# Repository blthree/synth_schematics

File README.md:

View this project on [CADLAB.io](https://cadlab.io/project/1908). 

# synth_schematics

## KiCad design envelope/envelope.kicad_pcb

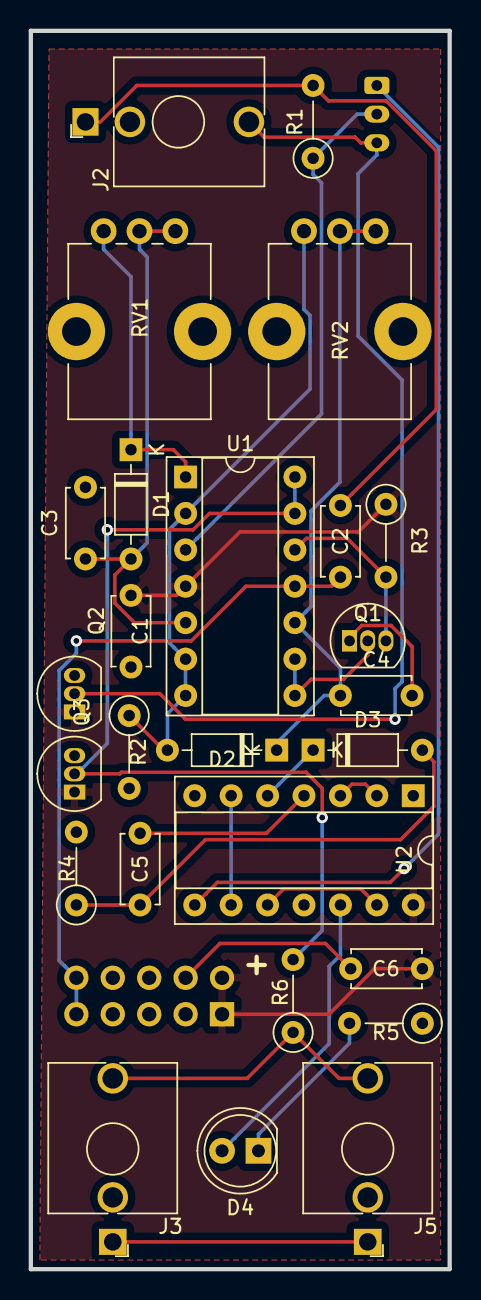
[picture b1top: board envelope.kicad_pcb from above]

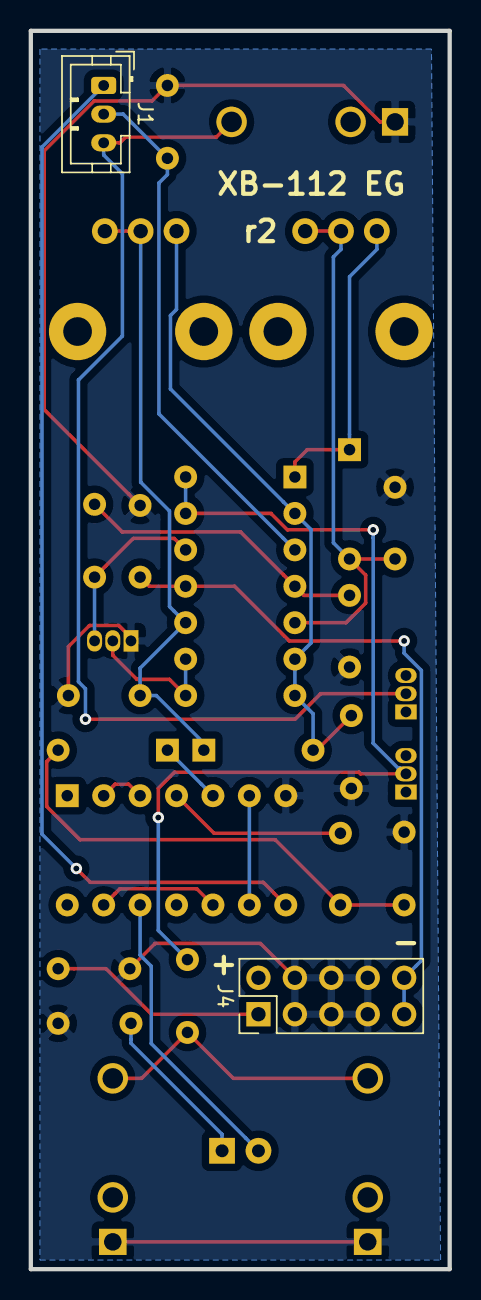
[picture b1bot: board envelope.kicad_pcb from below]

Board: 2 copper layers, 29.2 x 86.4 mm, 28 parts (2 on the bottom side), 22 nets.

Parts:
C1, C2, C6: 0.1uF; C_Disc_D4.7mm_W2.5mm_P5.00mm
C3, C4, C5: 1uF; C_Disc_D4.7mm_W2.5mm_P5.00mm
D1, D2: D_ALT; D_DO-35_SOD27_P7.62mm_Horizontal
D3: 1N4148; D_DO-35_SOD27_P7.62mm_Horizontal
D4: LED; LED_D5.0mm
J1: Sustain; JST_PH_B3B-PH-K_1x03_P2.00mm_Vertical
J2: Gate In; Jack_3.5mm_QingPu_WQP-PJ398SM_Vertical_CircularHoles
J3: Env Out 1; Jack_3.5mm_QingPu_WQP-PJ398SM_Vertical_CircularHoles
J4: Power; PinHeader_2x05_P2.54mm_Vertical
J5: Env Out 2; Jack_3.5mm_QingPu_WQP-PJ398SM_Vertical_CircularHoles
Q1: 2N3906; TO-92_Inline
Q2, Q3: BC548; TO-92_Inline
R1, R2: 1M; R_Axial_DIN0207_L6.3mm_D2.5mm_P5.08mm_Vertical
R3, R4: 100K; R_Axial_DIN0207_L6.3mm_D2.5mm_P5.08mm_Vertical
R5, R6: 1K; R_Axial_DIN0207_L6.3mm_D2.5mm_P5.08mm_Vertical
RV1: 1M Attack; Potentiometer_Bourns_PTV09A-1_Single_Vertical
RV2: 1M Decay; Potentiometer_Bourns_PTV09A-1_Single_Vertical
U1: TL074; DIP-14_W7.62mm_Socket
U2: 40106; DIP-14_W7.62mm_Socket

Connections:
+9V: C1.1, C6.1, J4.1, J4.2, Q2.1, Q3.1, R3.1, U1.4, U2.14
-9V: C2.1, J4.9, J4.10, U1.11
EG: J3.T, J5.T, R6.1
EG_In: J1.2, R1.1, U1.3
GND: C1.2, C2.2, C3.2, C4.2, C6.2, J2.S, J3.S, J4.3, J4.4, J4.5, J4.6, J4.7, J4.8, J5.S, Q1.1, R1.2, R2.2, R4.2, R5.1, U2.7
Gate: J1.3, J2.T, Q2.2
unnamed: C3.1, D1.2, RV1.2, RV1.3, U1.5
unnamed: C4.1, D2.1, RV2.2, RV2.3, U1.10
unnamed: C5.1, D3.2, R4.1
unnamed: C5.2, U2.4
unnamed: D1.1, RV1.1, U1.1
unnamed: D2.2, R2.1, RV2.1, U1.2, U1.6, U1.7
unnamed: D3.1, U2.5
unnamed: D4.1, R5.2
unnamed: D4.2, U2.12
unnamed: Q1.2, U1.8, U1.9
unnamed: Q1.3, R3.2, U1.12
unnamed: Q3.2, R6.2, U1.13, U1.14
unnamed: U2.2, U2.3
unnamed: U2.6, U2.9
unnamed: U2.10, U2.13
Trigger: J1.1, U2.8

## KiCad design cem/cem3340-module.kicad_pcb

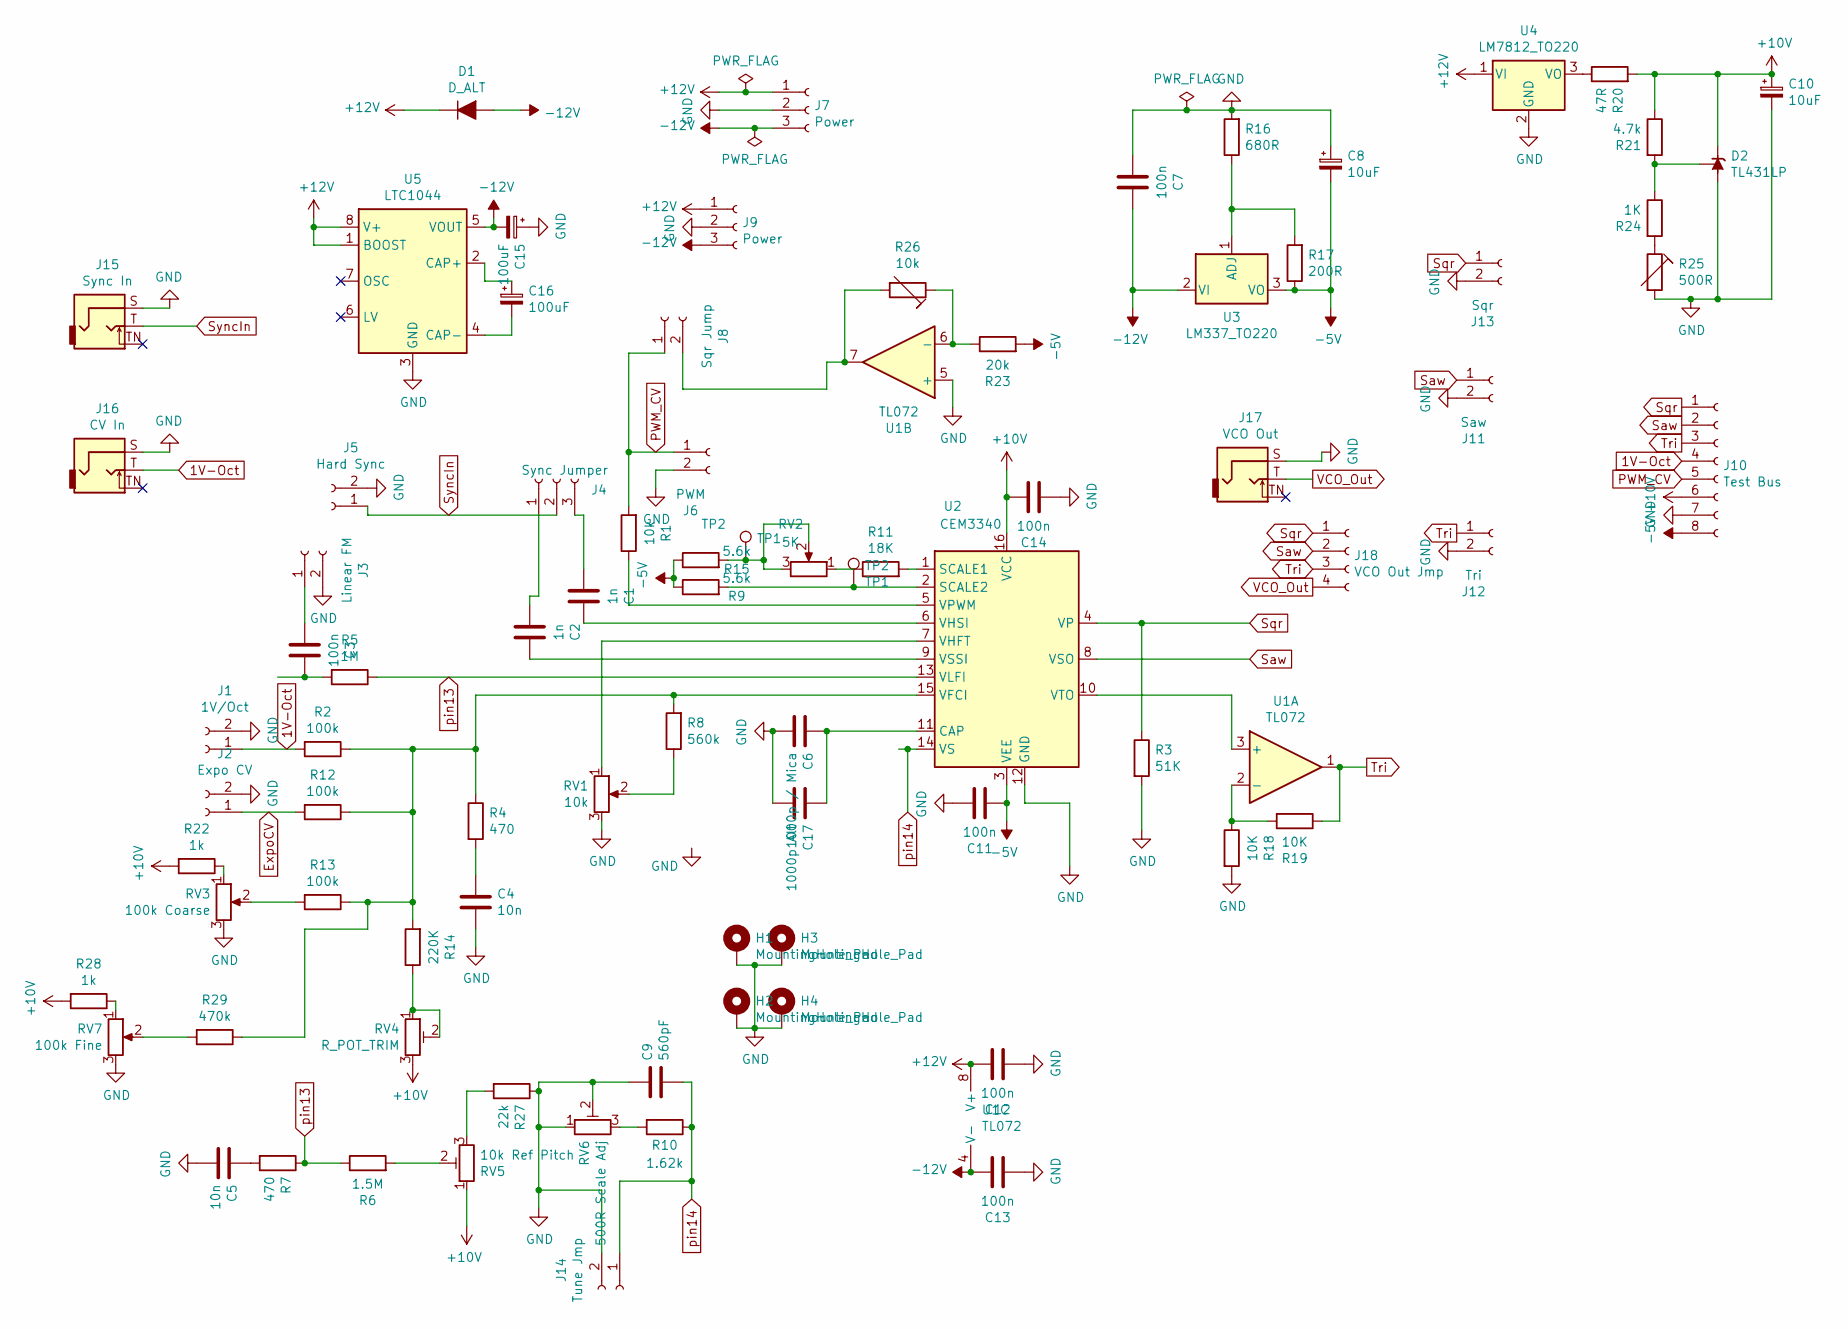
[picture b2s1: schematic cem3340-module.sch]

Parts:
C1, C2: 1n; C_Disc_D4.7mm_W2.5mm_P5.00mm
C3, C7, C11, C12, C13, C14: 100n; C_Disc_D4.7mm_W2.5mm_P5.00mm
C4, C5: 10n; C_Disc_D4.7mm_W2.5mm_P5.00mm
C6: 1000p / Mica; C_Axial_L12.0mm_D6.5mm_P15.00mm_Horizontal
C8, C10: 10uF; CP_Radial_D7.5mm_P2.50mm
C9: 560pF; C_Disc_D4.7mm_W2.5mm_P5.00mm
C15, C16: 100uF; CP_Radial_D7.5mm_P2.50mm
C17: 1000p Alt; C_Rect_L10.0mm_W4.0mm_P7.50mm_MKS4
D1: D_ALT; D_DO-35_SOD27_P7.62mm_Horizontal
D2: TL431LP; TO-92_Inline
H1, H2, H3, H4: MountingHole_Pad; MountingHole_3.2mm_M3_ISO14580_Pad
J1: 1V/Oct; PinHeader_1x02_P2.54mm_Vertical
J2: Expo CV; PinHeader_1x02_P2.54mm_Vertical
J3: Linear FM; PinHeader_1x02_P2.54mm_Vertical
J4: Sync Jumper; PinHeader_1x03_P2.54mm_Vertical
J5: Hard Sync; PinHeader_1x02_P2.54mm_Vertical
J6: PWM; PinHeader_1x02_P2.54mm_Vertical
J7: Power; JST_PH_B3B-PH-K_1x03_P2.00mm_Vertical
J8: Sqr Jump; PinHeader_1x02_P2.54mm_Vertical
J9: Power; JST_XH_B03B-XH-AM_1x03_P2.50mm_Vertical
J10: Test Bus; PinHeader_1x08_P2.54mm_Vertical
J11: Saw; PinHeader_1x02_P2.54mm_Vertical
J12: Tri; PinHeader_1x02_P2.54mm_Vertical
J13: Sqr; PinHeader_1x02_P2.54mm_Vertical
J14: Tune Jmp; PinHeader_1x02_P2.54mm_Vertical
J15: Sync In; CUI_SJ2-3592B-SMT-TR
J16: CV In; CUI_SJ2-3592B-SMT-TR
J17: VCO Out; CUI_SJ2-3592B-SMT-TR
J18: VCO Out Jmp; PinHeader_1x04_P2.54mm_Vertical
R1: 10k; R_Axial_DIN0207_L6.3mm_D2.5mm_P5.08mm_Vertical
R2, R12, R13: 100k; R_Axial_DIN0207_L6.3mm_D2.5mm_P5.08mm_Vertical
R3: 51K; R_Axial_DIN0207_L6.3mm_D2.5mm_P5.08mm_Vertical
R4, R7: 470; R_Axial_DIN0207_L6.3mm_D2.5mm_P5.08mm_Vertical
R5: 1M; R_Axial_DIN0207_L6.3mm_D2.5mm_P5.08mm_Vertical
R6: 1.5M; R_Axial_DIN0207_L6.3mm_D2.5mm_P5.08mm_Vertical
R8: 560k; R_Axial_DIN0207_L6.3mm_D2.5mm_P5.08mm_Vertical
R9, R15: 5.6k; R_Axial_DIN0207_L6.3mm_D2.5mm_P5.08mm_Vertical
R10: 1.62k; R_Axial_DIN0207_L6.3mm_D2.5mm_P5.08mm_Vertical
R11: 18K; R_Axial_DIN0207_L6.3mm_D2.5mm_P5.08mm_Vertical
R14: 220K; R_Axial_DIN0207_L6.3mm_D2.5mm_P5.08mm_Vertical
R16: 680R; R_Axial_DIN0207_L6.3mm_D2.5mm_P5.08mm_Vertical
R17: 200R; R_Axial_DIN0207_L6.3mm_D2.5mm_P5.08mm_Vertical
R18, R19: 10K; R_Axial_DIN0207_L6.3mm_D2.5mm_P5.08mm_Vertical
R20: 47R; R_Axial_DIN0207_L6.3mm_D2.5mm_P5.08mm_Vertical
R21: 4.7k; R_Axial_DIN0207_L6.3mm_D2.5mm_P5.08mm_Vertical
R22, R28: 1k; R_Axial_DIN0207_L6.3mm_D2.5mm_P5.08mm_Vertical
R23: 20k; R_Axial_DIN0207_L6.3mm_D2.5mm_P5.08mm_Vertical
R24: 1K; R_Axial_DIN0207_L6.3mm_D2.5mm_P5.08mm_Vertical
R25: 500R; Potentiometer_Bourns_3296W_Vertical
R26: 10k; Potentiometer_Bourns_3296W_Vertical
R27: 22k; R_Axial_DIN0207_L6.3mm_D2.5mm_P5.08mm_Vertical
R29: 470k; R_Axial_DIN0207_L6.3mm_D2.5mm_P5.08mm_Vertical
RV1: 10k; Potentiometer_Bourns_3296W_Vertical
RV2: 5K; Potentiometer_Bourns_3386P_Vertical
RV3: 100k Coarse; Potentiometer_Bourns_PTV09A-1_Single_Vertical
RV4: R_POT_TRIM; Potentiometer_Bourns_3296W_Vertical
RV5: 10k Ref Pitch; Potentiometer_Bourns_3296W_Vertical
RV6: 500R Scale Adj; Potentiometer_Bourns_3296W_Vertical
RV7: 100k Fine; Potentiometer_Bourns_PTV09A-1_Single_Vertical
TP1: TP2; TestPoint_Pad_2.5x2.5mm
TP2: TP1; TestPoint_Pad_D2.5mm
U1: TL072; DIP-8_W7.62mm_Socket
U2: CEM3340; DIP-16_W7.62mm_Socket
U3: LM337_TO220; TO-220-3_Horizontal_TabDown
U4: LM7812_TO220; TO-220-3_Horizontal_TabDown
U5: LTC1044; DIP-8_W7.62mm_Socket

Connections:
1V-Oct: J1.1, J10.4, J16.T, R2.2
+10V: C10.1, C14.1, D2.3 (K), J10.6, R20.2, R21.1, R22.2, R28.2, RV4.3, RV5.1, U2.16 (VCC)
+12V: C12.1, D1.1 (K), J7.1, J9.1, U1.8 (V+), U4.1 (VI), U5.1 (BOOST), U5.8 (V+)
-5V: C8.2, C11.2, J10.8, R9.1, R15.1, R17.1, R23.2, U2.3 (VEE), U3.3 (VO)
-12V: C7.1, C13.1, C15.2, D1.2 (A), J7.3, J9.3, U1.4 (V-), U3.2 (VI), U5.5 (VOUT)
ExpoCV: J2.1, R12.2
GND: C4.2, C5.2, C6.2, C7.2, C8.1, C9.1, C10.2, C11.1, C12.2, C13.2, C14.2, C15.1, C17.2, D2.2 (A), H1.1, H2.1, H3.1, H4.1, J1.2, J2.2, J3.2, J5.2, J6.2, J7.2, J9.2, J10.7, J11.2, J12.2, J13.2, J14.2, J15.S, J16.S, J17.S, R3.2, R16.2, R18.2, R25.2, R27.1, RV1.3, RV3.3, RV6.1, RV6.2, RV7.3, U1.5 (+), U2.12 (GND), U4.2 (GND), U5.3 (GND)
unnamed: C1.1, U2.6 (VHSI)
unnamed: C1.2, J4.3
unnamed: C2.1, U2.9 (VSSI)
unnamed: C2.2, J4.1
unnamed: C3.1, R5.2
unnamed: C3.2, J3.1
unnamed: C4.1, R4.2
unnamed: C5.1, R7.2
unnamed: C16.1, U5.2 (CAP+)
unnamed: C16.2, U5.4 (CAP-)
unnamed: C6.1, C17.1, U2.11 (CAP)
unnamed: D2.1 (REF), R21.2, R24.1
unnamed: J8.2, R26.2, U1.7
unnamed: R1.1, U2.5 (VPWM)
unnamed: R6.2, RV5.2
unnamed: R8.1, RV1.2
unnamed: R9.2, TP2.1, U2.2 (SCALE2)
unnamed: R10.2, RV6.3
unnamed: R11.1, RV2.1
unnamed: R11.2, U2.1 (SCALE1)
unnamed: R2.1, R4.1, R8.2, R12.1, R13.1, R14.2, R29.1, U2.15 (VFCI)
unnamed: R13.2, RV3.2
unnamed: R14.1, RV4.1, RV4.2
unnamed: R15.2, RV2.2, RV2.3, TP1.1
unnamed: R16.1, R17.2, U3.1 (ADJ)
unnamed: R18.1, R19.2, U1.2 (-)
unnamed: R20.1, U4.3 (VO)
unnamed: R22.1, RV3.1
unnamed: R23.1, R26.1, U1.6 (-)
unnamed: R24.2, R25.1
unnamed: R27.2, RV5.3
unnamed: R28.1, RV7.1
unnamed: R29.2, RV7.2
unnamed: RV1.1, U2.7 (VHFT)
unnamed: U1.3 (+), U2.10 (VTO)
PWM_CV: J6.1, J8.1, J10.5, R1.2
Saw: J10.2, J11.1, J18.2, U2.8 (VSO)
Sqr: J10.1, J13.1, J18.1, R3.1, U2.4 (VP)
SyncIn: J4.2, J5.1, J15.T
Tri: J10.3, J12.1, J18.3, R19.1, U1.1
VCO_Out: J17.T, J18.4
pin13: R5.1, R6.1, R7.1, U2.13 (VLFI)
pin14: C9.2, J14.1, R10.1, U2.14 (VS)

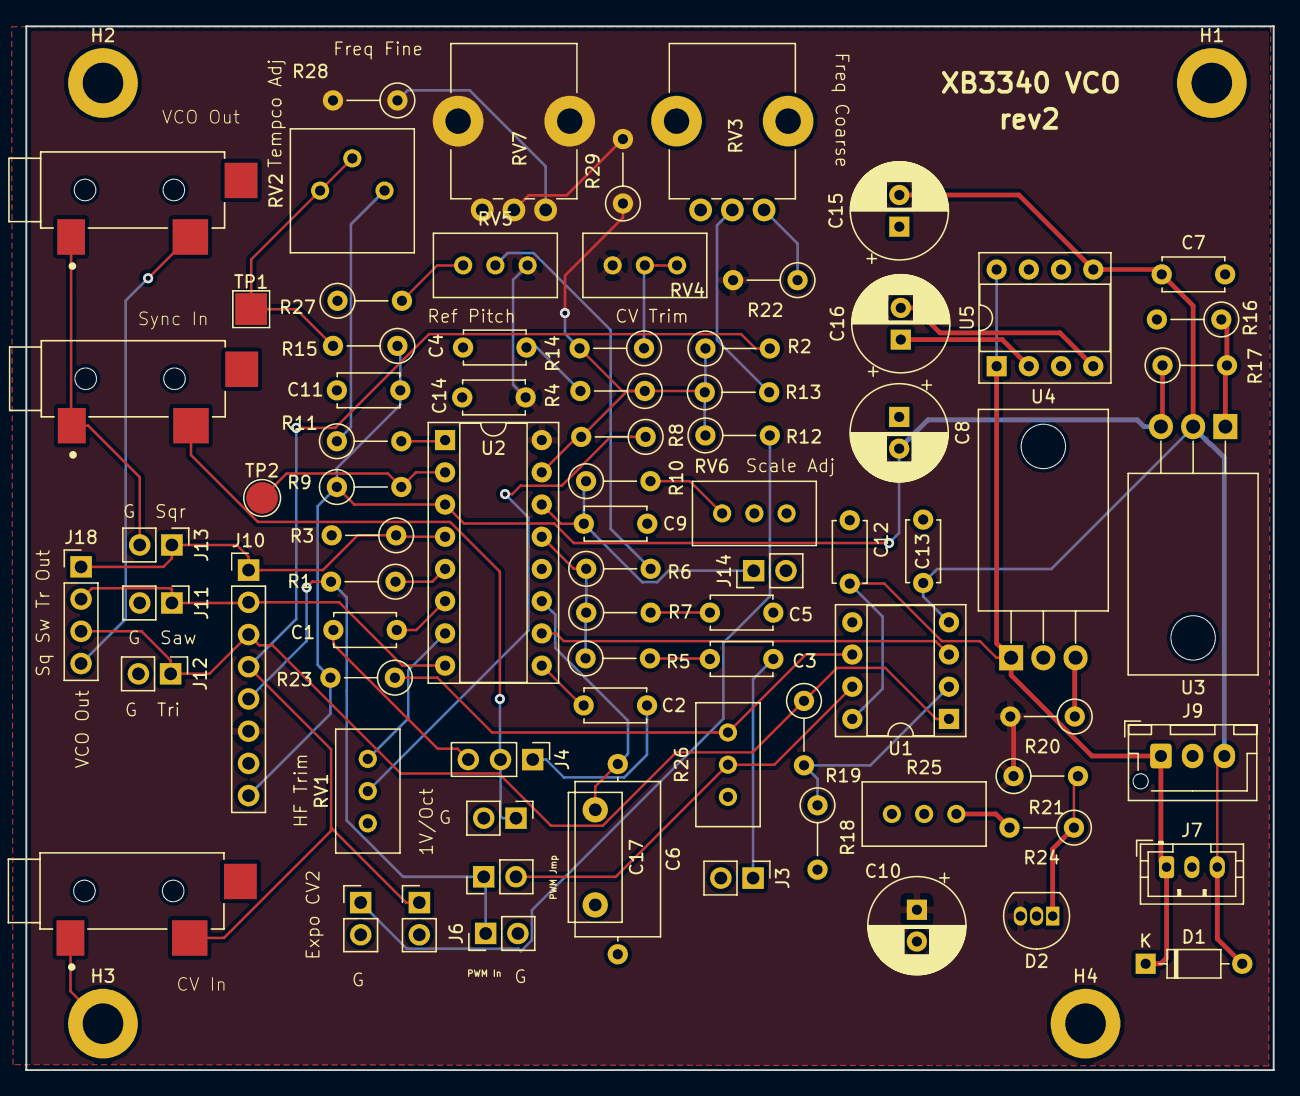
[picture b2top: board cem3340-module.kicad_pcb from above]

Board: 2 copper layers, 98.3 x 82.3 mm, 84 parts (0 on the bottom side), 50 nets.

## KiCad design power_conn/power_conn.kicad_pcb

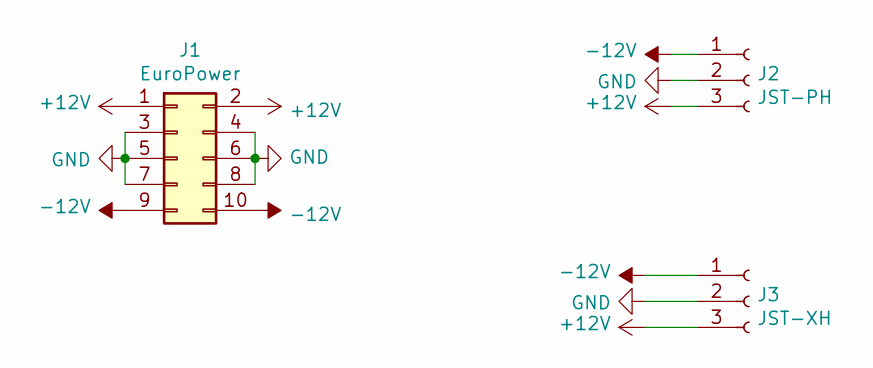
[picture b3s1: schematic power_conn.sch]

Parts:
J1: EuroPower; PinSocket_2x05_P2.54mm_Vertical
J2: JST-PH; JST_PH_B3B-PH-K_1x03_P2.00mm_Vertical
J3: JST-XH; JST_XH_B3B-XH-AM_1x03_P2.50mm_Vertical

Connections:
+12V: J1.1, J1.2, J2.3, J3.3
-12V: J1.9, J1.10, J2.1, J3.1
GND: J1.3, J1.4, J1.5, J1.6, J1.7, J1.8, J2.2, J3.2

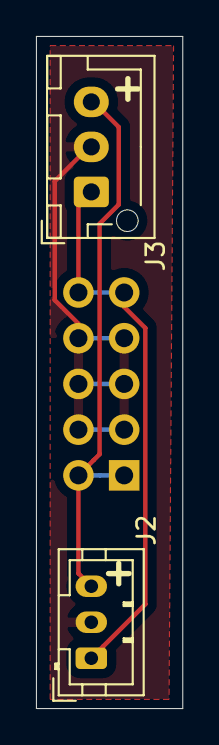
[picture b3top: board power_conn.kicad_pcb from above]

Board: 2 copper layers, 8.1 x 37.3 mm, 3 parts (1 on the bottom side), 3 nets.

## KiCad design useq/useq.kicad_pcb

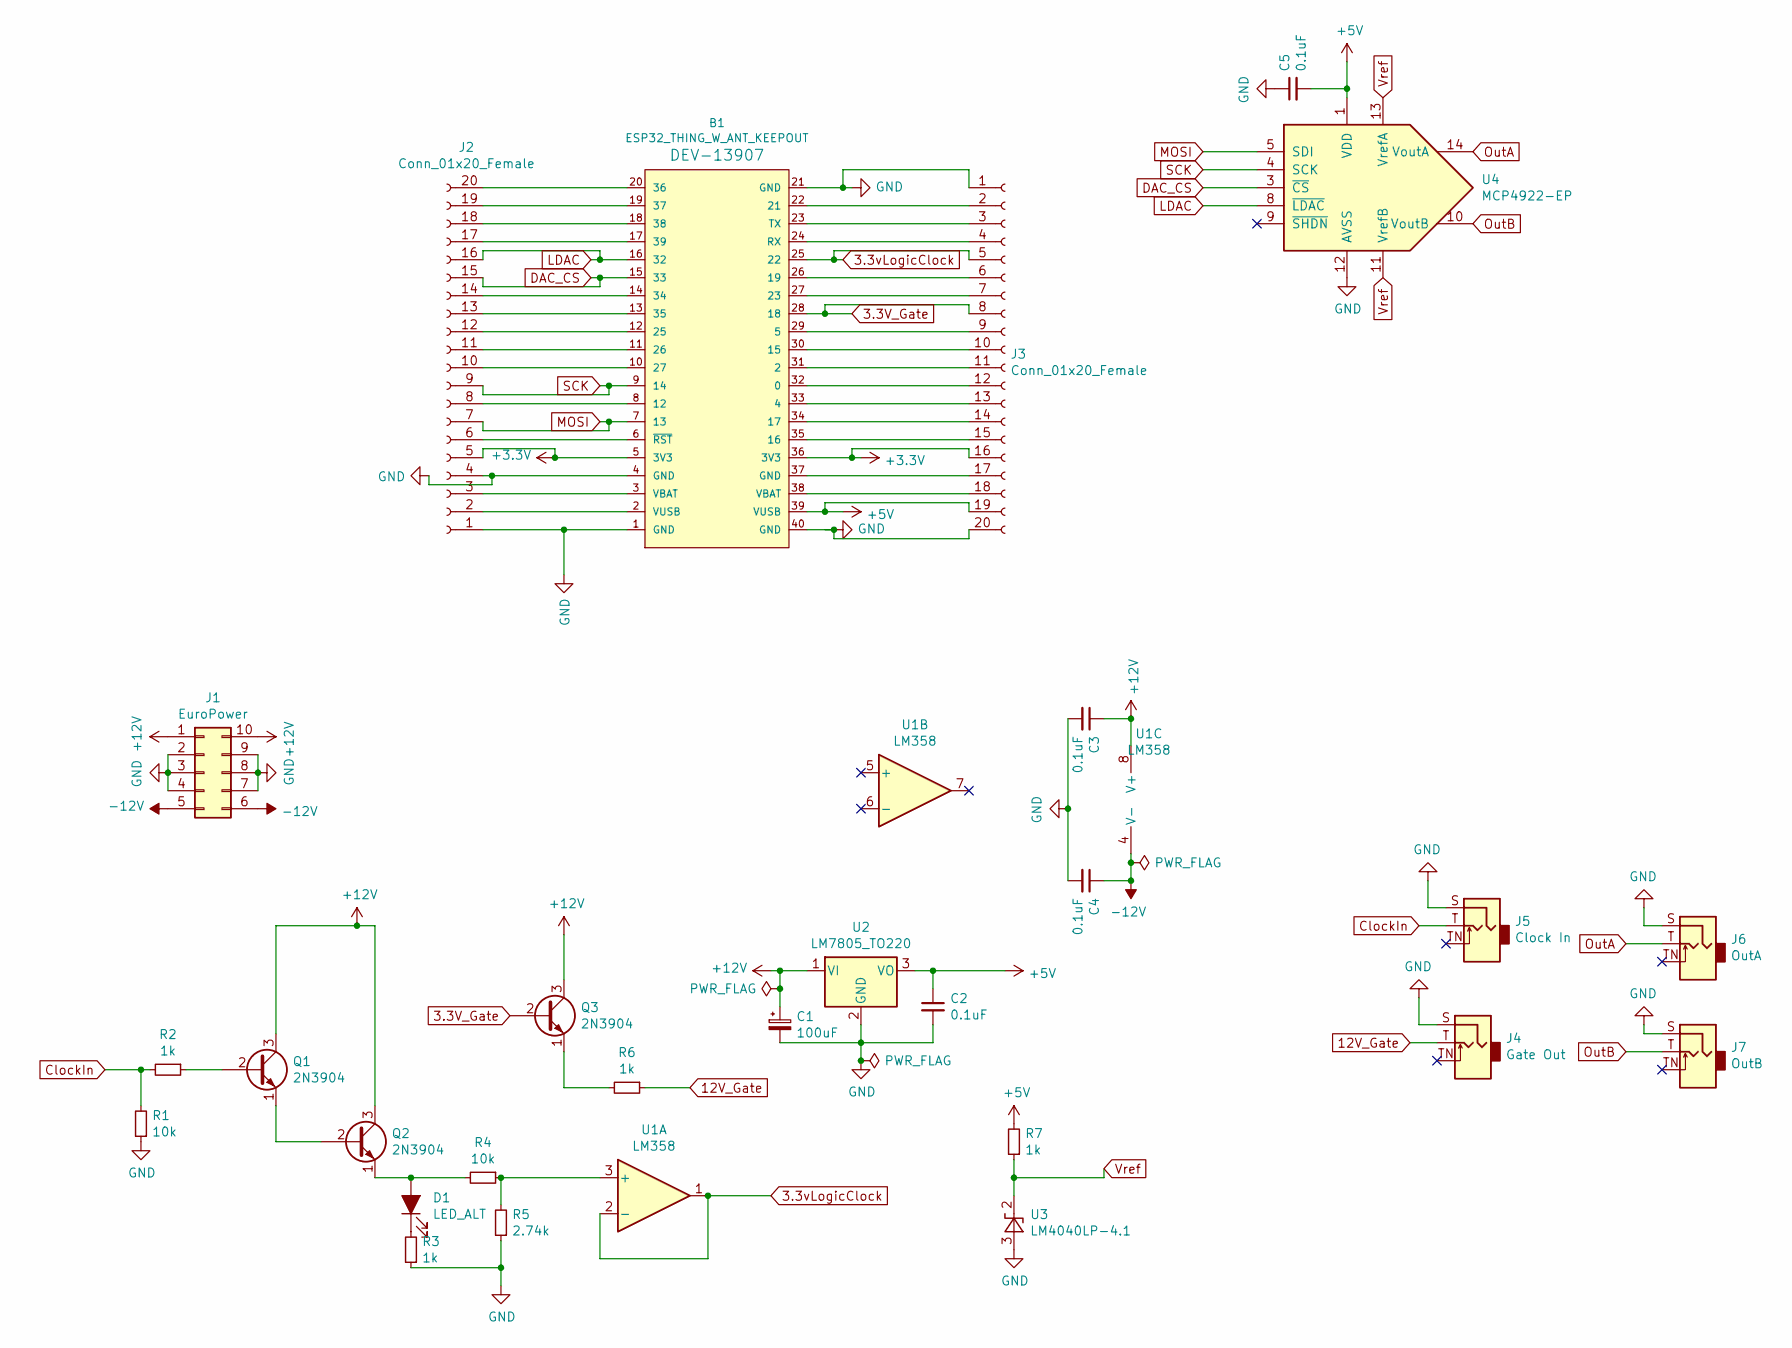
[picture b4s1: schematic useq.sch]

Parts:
B1: ESP32_THING_W_ANT_KEEPOUT; ESP32_THING
C1: 100uF; CP_Radial_D5.0mm_P2.50mm
C2, C3, C4, C5: 0.1uF; C_Disc_D4.7mm_W2.5mm_P5.00mm
D1: LED_ALT; LED_D5.0mm
J1: EuroPower; PinHeader_2x05_P2.54mm_Vertical
J2, J3: Conn_01x20_Female; PinSocket_1x20_P2.54mm_Vertical
J4: Gate Out; Jack_3.5mm_QingPu_WQP-PJ398SM_Vertical_CircularHoles
J5: Clock In; Jack_3.5mm_QingPu_WQP-PJ398SM_Vertical_CircularHoles
J6: OutA; Jack_3.5mm_QingPu_WQP-PJ398SM_Vertical_CircularHoles
J7: OutB; Jack_3.5mm_QingPu_WQP-PJ398SM_Vertical_CircularHoles
Q1, Q2, Q3: 2N3904; TO-92_Inline
R1, R4: 10k; R_Axial_DIN0207_L6.3mm_D2.5mm_P5.08mm_Vertical
R2, R3, R6, R7: 1k; R_Axial_DIN0207_L6.3mm_D2.5mm_P5.08mm_Vertical
R5: 2.74k; R_Axial_DIN0207_L6.3mm_D2.5mm_P5.08mm_Vertical
U1: LM358; DIP-8_W7.62mm_Socket
U2: LM7805_TO220; TO-220-3_Horizontal_TabDown
U3: LM4040LP-4.1; TO-92_Inline
U4: MCP4922-EP; DIP-14_W7.62mm_Socket

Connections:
3.3V_Gate: B1.28 (18), J3.8, Q3.2 (B)
3.3vLogicClock: B1.25 (22), J3.5, U1.1, U1.2 (-)
12V_Gate: J4.T, R6.1
+3V3: B1.5 (3V3), B1.36 (3V3), J2.5, J3.16
+5V: B1.39 (VUSB), C2.1, C5.2, J3.19, R7.2, U2.3 (VO), U4.1 (VDD)
+12V: C1.1, C3.1, J1.1, J1.10, Q1.3 (C), Q2.3 (C), Q3.3 (C), U1.8 (V+), U2.1 (VI)
-12V: C4.1, J1.5, J1.6, U1.4 (V-)
ClockIn: J5.T, R1.2, R2.2
DAC_CS: B1.15 (33), J2.15, U4.3 (~CS~)
GND: B1.1 (GND), B1.4 (GND), B1.21 (GND), B1.40 (GND), C1.2, C2.2, C3.2, C4.2, C5.1, J1.2, J1.3, J1.4, J1.7, J1.8, J1.9, J2.1, J2.4, J3.1, J3.20, J4.S, J5.S, J6.S, J7.S, R1.1, R3.1, R5.1, U2.2 (GND), U3.3 (A), U4.12 (AVSS)
LDAC: B1.16 (32), J2.16, U4.8 (~LDAC~)
MOSI: B1.7 (13), J2.7, U4.5 (SDI)
unnamed: B1.2 (VUSB), J2.2
unnamed: B1.3 (VBAT), J2.3
unnamed: B1.6 (~RST~), J2.6
unnamed: B1.8 (12), J2.8
unnamed: B1.10 (27), J2.10
unnamed: B1.11 (26), J2.11
unnamed: B1.12 (25), J2.12
unnamed: B1.13 (35), J2.13
unnamed: B1.14 (34), J2.14
unnamed: B1.17 (39), J2.17
unnamed: B1.18 (38), J2.18
unnamed: B1.19 (37), J2.19
unnamed: B1.20 (36), J2.20
unnamed: B1.22 (21), J3.2
unnamed: B1.23 (TX), J3.3
unnamed: B1.24 (RX), J3.4
unnamed: B1.26 (19), J3.6
unnamed: B1.27 (23), J3.7
unnamed: B1.29 (5), J3.9
unnamed: B1.30 (15), J3.10
unnamed: B1.31 (2), J3.11
unnamed: B1.32 (0), J3.12
unnamed: B1.33 (4), J3.13
unnamed: B1.34 (17), J3.14
unnamed: B1.35 (16), J3.15
unnamed: B1.37 (GND), J3.17
unnamed: B1.38 (VBAT), J3.18
unnamed: D1.1 (K), R3.2
unnamed: D1.2 (A), Q2.1 (E), R4.2
unnamed: Q1.1 (E), Q2.2 (B)
unnamed: Q1.2 (B), R2.1
unnamed: Q3.1 (E), R6.2
unnamed: R4.1, R5.2, U1.3 (+)
OutA: J6.T, U4.14 (VoutA)
OutB: J7.T, U4.10 (VoutB)
SCK: B1.9 (14), J2.9, U4.4 (SCK)
Vref: R7.1, U3.2 (K), U4.11 (VrefB), U4.13 (VrefA)

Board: 2 copper layers, 28 parts (5 on the bottom side), 49 nets, no tracks yet.

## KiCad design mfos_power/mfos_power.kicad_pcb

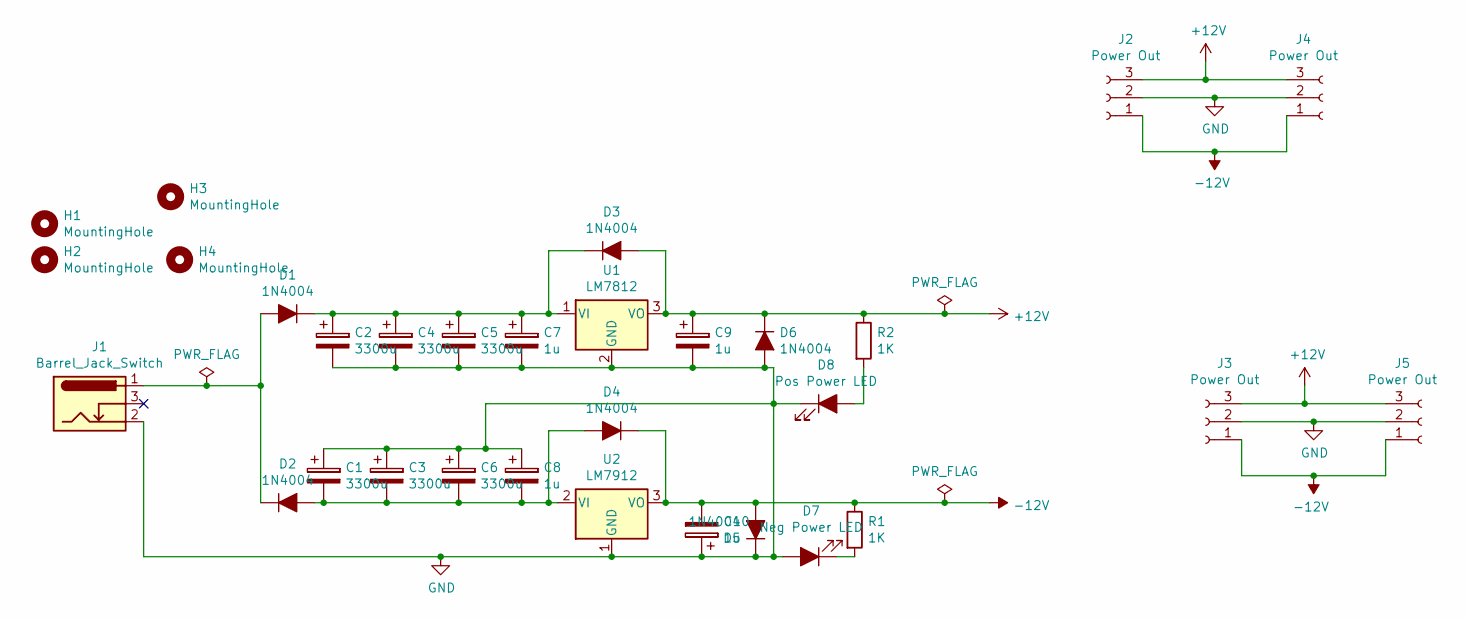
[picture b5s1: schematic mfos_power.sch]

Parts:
C1, C2, C3, C4, C5, C6: 3300u; CP_Radial_D18.0mm_P7.50mm
C7, C8, C9, C10: 1u; CP_Radial_D6.3mm_P2.50mm
D1, D2, D3, D4, D5, D6: 1N4004; D_DO-41_SOD81_P10.16mm_Horizontal
D7: Neg Power LED; LED_D5.0mm
D8: Pos Power LED; LED_D5.0mm
H1, H2, H3, H4: MountingHole; MountingHole_3.2mm_M3_ISO7380
J1: Barrel_Jack_Switch; BarrelJack_CUI_PJ-102AH_Horizontal
J2, J3: Power Out; JST_PH_B3B-PH-K_1x03_P2.00mm_Vertical
J4, J5: Power Out; JST_XH_B03B-XH-A_1x03_P2.50mm_Vertical
R1, R2: 1K; R_Axial_DIN0207_L6.3mm_D2.5mm_P5.08mm_Vertical
U1: LM7812; TO-220-3_Horizontal_TabDown
U2: LM7912; TO-220-3_Horizontal_TabDown

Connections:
+12V: C9.1, D3.2 (A), D6.1 (K), J2.3, J3.3, J4.3, J5.3, R2.1, U1.3 (VO)
-12V: C10.2, D4.1 (K), D5.2 (A), J2.1, J3.1, J4.1, J5.1, R1.1, U2.3 (VO)
GND: C1.1, C2.2, C3.1, C4.2, C5.2, C6.1, C7.2, C8.1, C9.2, C10.1, D5.1 (K), D6.2 (A), D7.2 (A), D8.1 (K), J1.2, J2.2, J3.2, J4.2, J5.2, U1.2 (GND), U2.1 (GND)
unnamed: C1.2, C3.2, C6.2, C8.2, D2.2 (A), D4.2 (A), U2.2 (VI)
unnamed: C2.1, C4.1, C5.1, C7.1, D1.1 (K), D3.1 (K), U1.1 (VI)
unnamed: D1.2 (A), D2.1 (K), J1.1
unnamed: D7.1 (K), R1.2
unnamed: D8.2 (A), R2.2

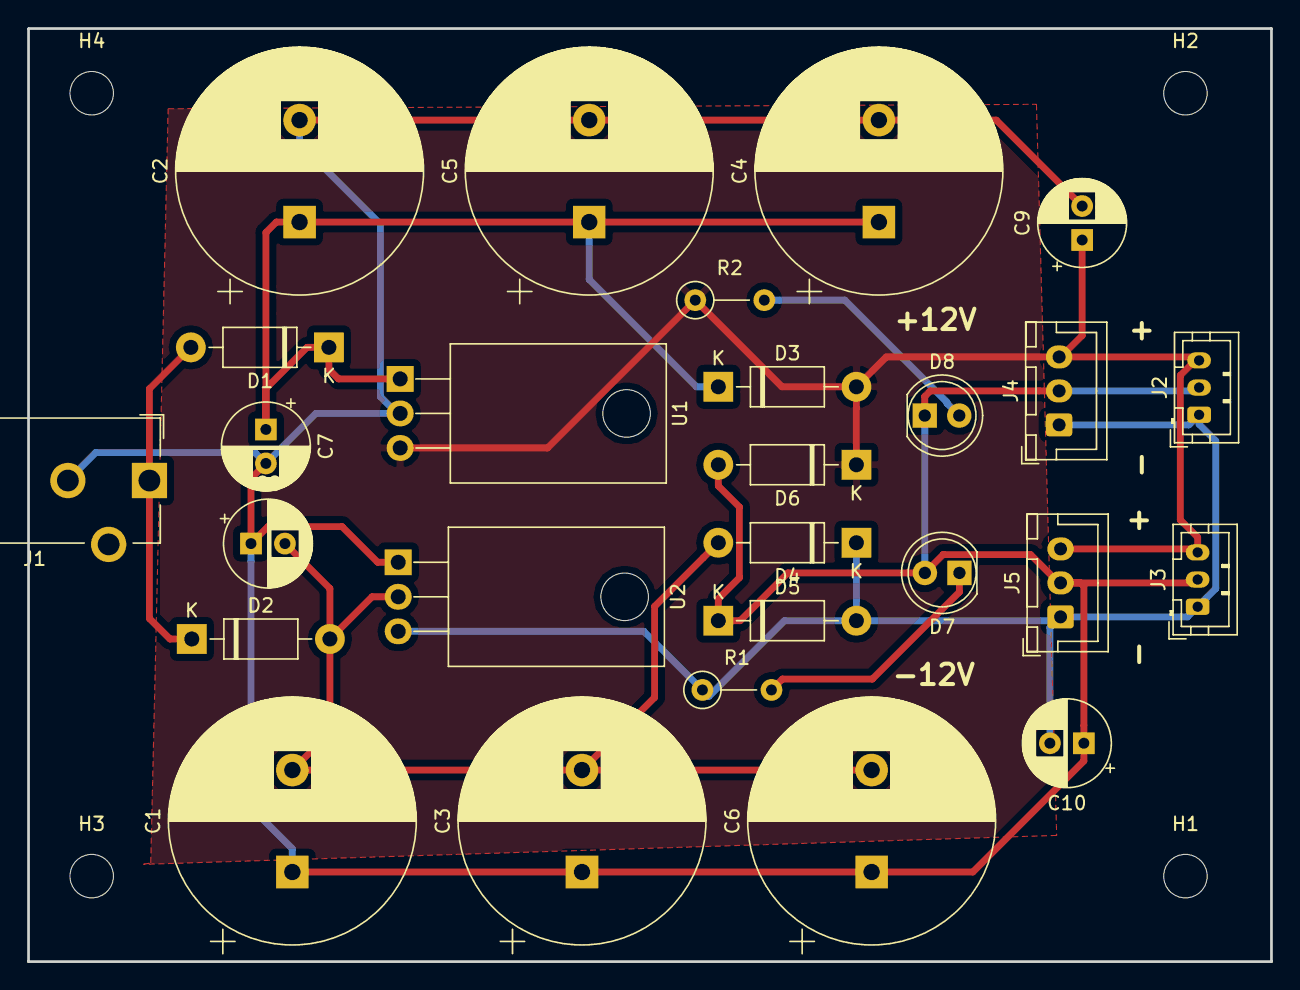
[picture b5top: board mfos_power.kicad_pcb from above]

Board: 2 copper layers, 91.5 x 68.7 mm, 31 parts (0 on the bottom side), 8 nets.

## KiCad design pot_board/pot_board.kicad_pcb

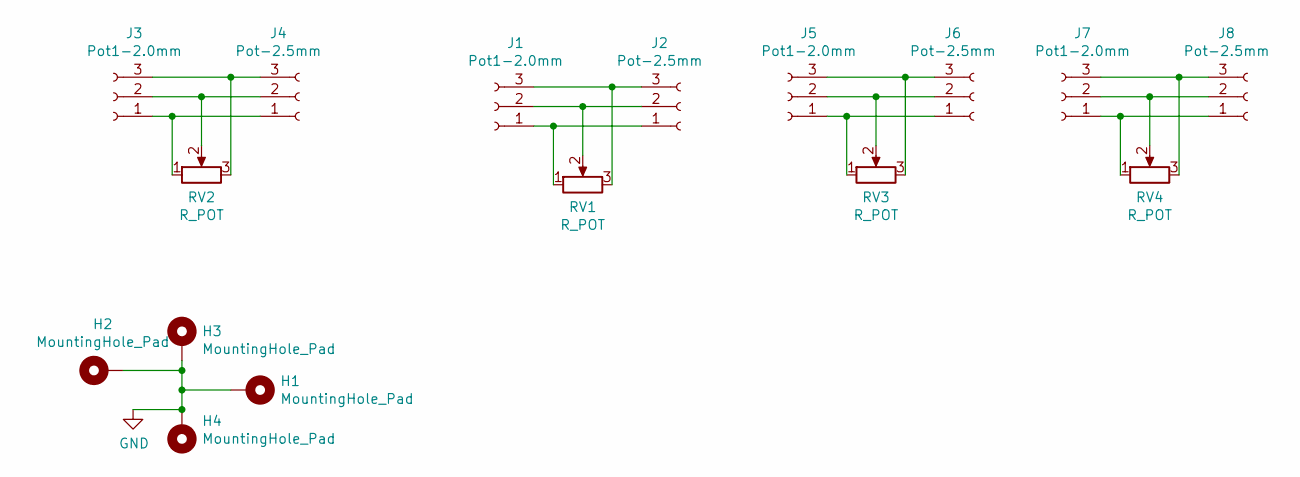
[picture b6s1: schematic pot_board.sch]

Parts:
H1, H2, H3, H4: MountingHole_Pad; MountingHole_3.2mm_M3_ISO7380_Pad
J1, J3, J5, J7: Pot1-2.0mm; JST_PH_B3B-PH-K_1x03_P2.00mm_Vertical
J2, J4, J6, J8: Pot-2.5mm; JST_XH_B03B-XH-A_1x03_P2.50mm_Vertical
RV1, RV2, RV3, RV4: R_POT; Potentiometer_Bourns_PTV09A-1_Single_Vertical

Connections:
GND: H1.1, H2.1, H3.1, H4.1
unnamed: J1.1, J2.1, RV1.1
unnamed: J1.2, J2.2, RV1.2
unnamed: J1.3, J2.3, RV1.3
unnamed: J3.1, J4.1, RV2.1
unnamed: J3.2, J4.2, RV2.2
unnamed: J3.3, J4.3, RV2.3
unnamed: J5.1, J6.1, RV3.1
unnamed: J5.2, J6.2, RV3.2
unnamed: J5.3, J6.3, RV3.3
unnamed: J7.1, J8.1, RV4.1
unnamed: J7.2, J8.2, RV4.2
unnamed: J7.3, J8.3, RV4.3

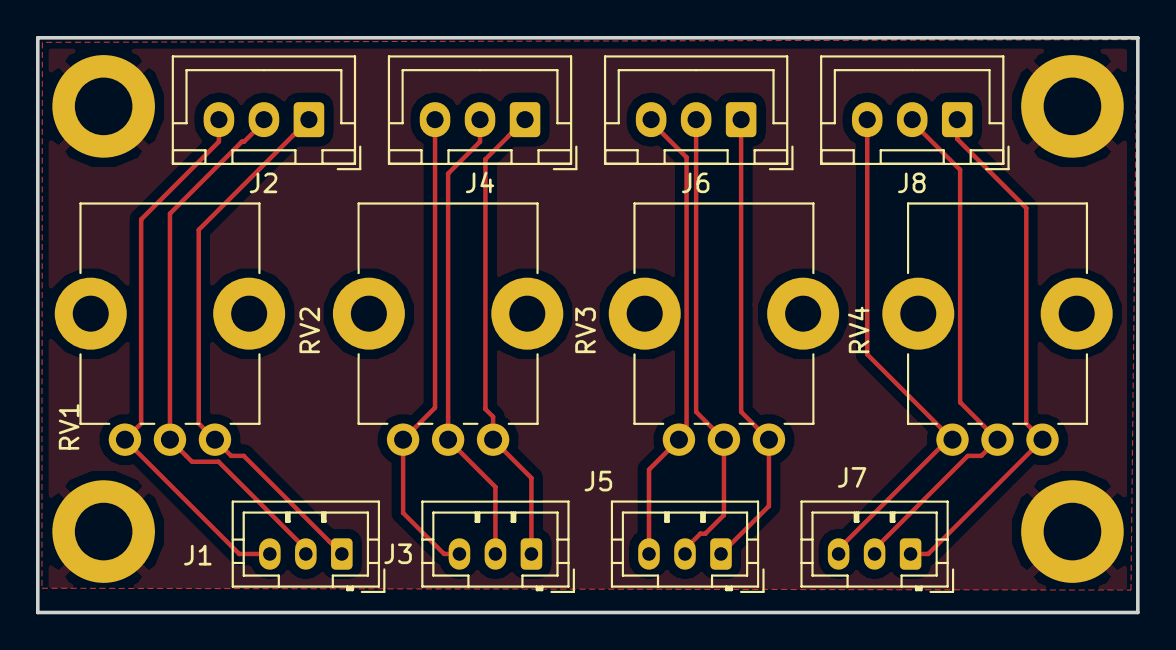
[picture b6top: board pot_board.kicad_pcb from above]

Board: 2 copper layers, 61.1 x 31.9 mm, 16 parts (0 on the bottom side), 13 nets.
